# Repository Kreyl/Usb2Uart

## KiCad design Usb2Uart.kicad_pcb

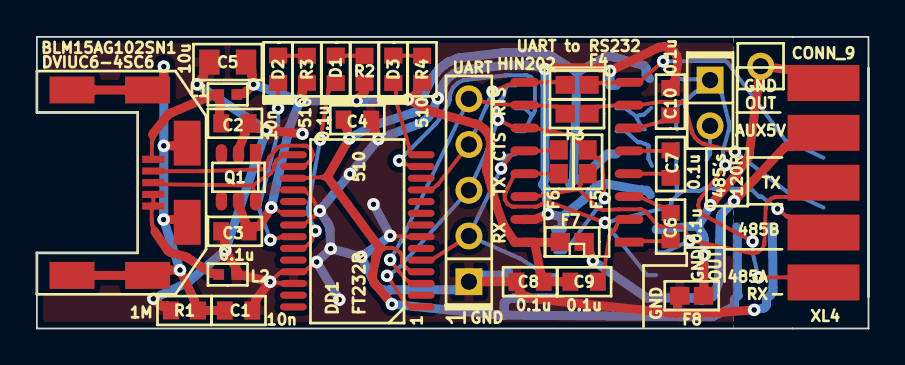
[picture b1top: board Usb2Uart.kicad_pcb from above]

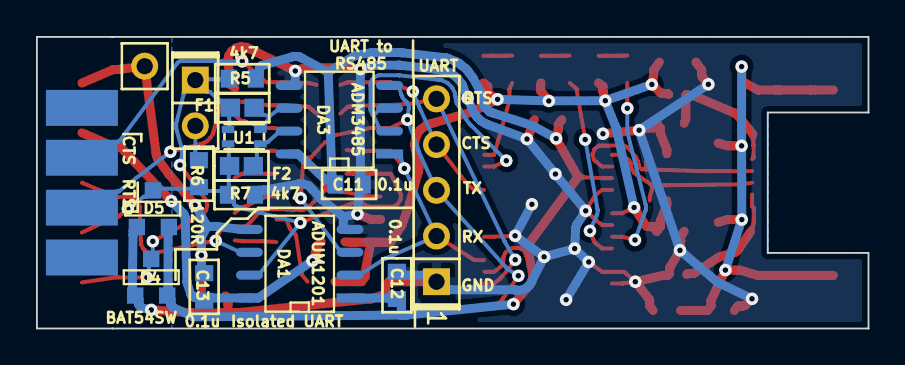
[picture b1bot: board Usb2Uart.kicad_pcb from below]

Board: 2 copper layers, 46.2 x 16.2 mm, 46 parts (13 on the bottom side), 35 nets.

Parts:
C1, C2: 10n; CAP_0603
C3, C4, C6, C7, C8, C9, C10, C11, C12, C13: 0.1u; CAP_0603
C5: 10u; CAP_0805
D1, D2, D3: LED; SMD_0603
D4, D5: BAT54SW; SOT23-3
DA1: ADUM1201; SO8
DA2: HIN202; SO16_150
DA3: ADM3485; SO8
DD1: FT232R; SSOP28
F1, F2: FUSE0R; RES_0603_FUSE
F3, F4, F5, F6, F7, F8: Fuse0R; RES_0603_FUSE
L1, L2: BLM15AG102SN1; IND_0402
Q1: DVIUC6-4SC6; SOT23-6
R1: 1M; RES_0603
R2, R3, R4: 510; RES_0603
R5, R7: 4k7; RES_0603
R6: 120R; RES_0603
U1: DLW21SN900SQ2; DLW21SN
XL1: USB_MICRO_B; USBmicro_MOLEX_WM17142
XL2: CONN_2; PLS-2
XL3: CONN_5; PLS-5
XL4: CONN_9; DB9_EDGE
XL5: CONN_1; PLS-1Rnd

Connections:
+3.3V: C4.1, C11.1, C12.2, D4.2, D5.2, DA1.1, DA3.8, DD1.4, DD1.17, R5.1
+5V: C3.2, C5.2, C8.2, C9.2, DA2.16, DD1.20, F7.2, L1.1, Q1.5, R2.1, R3.1, R4.1
/A: DA3.6, F1.2, U1.4
/Aux5V: C13.2, DA1.8, F7.1, XL4.4
/B: DA3.7, F2.2, U1.1
/CTS: DA2.8, F4.1, XL4.8
/D+: DD1.15, Q1.6, XL1.3
/D-: DD1.16, Q1.1, XL1.2
/PwrOn_LED: D3.C, DD1.14
/RS485A: D4.3, F1.1, R5.2, U1.3, XL2.1, XL4.1
/RS485B_RX: D5.3, DA1.7, DA2.13, F2.1, F6.1, R6.2, R7.1, U1.2, XL4.2
/RTS: DA2.7, F3.1, XL4.7
/RX_LED: D2.C, DD1.22
/SHLD: C1.1, R1.1, XL1.SHLD
/TX: DA1.6, DA2.14, F5.1, XL4.3
/TXDEN: DA3.2, DA3.3, DD1.13
/TX_LED: D1.C, DD1.23
/UART_CTS: DA2.9, DD1.11, F4.2, XL3.4
/UART_RTS: DA2.10, DD1.3, F3.2, XL3.5
/UART_RX: DA1.2, DA2.12, DA3.1, DD1.5, F6.2, XL3.2
/UART_TX: DA1.3, DA2.11, DA3.4, DD1.1, F5.2, XL3.3
/USB_IN_1: C2.2, L1.2, XL1.1
/USB_IN_2: L2.2, XL1.4, XL1.5
GND: C1.2, C2.1, C3.1, C4.2, C5.1, C8.1, C10.2, C11.2, C12.1, D4.1, D5.1, DA1.4, DA2.15, DA3.5, DD1.7, DD1.18, DD1.21, DD1.25, DD1.26, F8.2, L2.1, Q1.2, R1.2, R7.2, XL3.1
GNDPWR: C13.1, DA1.5, F8.1, XL4.5, XL5.1
unnamed: C6.1, DA2.3
unnamed: C6.2, DA2.1
unnamed: C7.1, DA2.5
unnamed: C7.2, DA2.4
unnamed: C9.1, DA2.2
unnamed: C10.1, DA2.6
unnamed: D1.A, R2.2
unnamed: D2.A, R3.2
unnamed: D3.A, R4.2
unnamed: R6.1, XL2.2

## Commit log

2015-10-20 + Old PCB
2015-10-22 Connector mirrored as it should be
2015-10-22 toporrrrrr
2015-10-24 gerber add
